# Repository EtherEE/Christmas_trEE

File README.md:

# Christmas tree lamp
> Christmas tree lamp prepared for a child's school Christmas market.

## Table of contents
* [General info](#general-info)
* [Topology](#topology)
* [Technologies](#technologies)
* [PCB](#pcb)
* [Setup](#setup)
* [Main components selection](#main-components-selection)
* [Status](#status)
* [License](#license)

## General info
Luminous Christmas tree-shaped light controlled by touch/proximity. The lamp uses a side-lit fiber optic as the luminous element. The light source is an LED module in white color. LED modules in red, green, blue are also available. Changing the LED module will require setting a different supply voltage on the DC/DC inverter and current verification. The lamp is powered by a battery. The capacity of the battery is sufficient to power the lamp through the night. The battery is charged via a USB type C port. The maximum total current of charging and lighting does not exceed 1 A. When the battery is charging, the D2 LED is lit, which produces a blue glow under the base of the lamp. The skeleton of the lamp and the embedding of the side-lighting fiber on it is a matter of individual taste. This is the most difficult part of the project and its execution directly affects the final result. I built the skeleton from stiff cardboard reinforced with wikol glue and wrapped the skeleton with white yarn. I mounted the LED module on plastic flat bars and glued them with hot glue to the inner parts of the skeleton.
Base width: 14 cm. The height of the lamp is 33 cm. 

## Topology

## Technologies
* Main luminous technology: Mentor M-FIBRE
* KiCAD as an EDA

## PCB

## Setup
Battery charging from USB type C socket with 500mA current set with PROG resistor R2 of 2k.
Sensor touch/proximity sensitivity adjustable with capacitor C7.

## Main components selection
* LED module
  Mentor 1330.0002; White; 1W; 3,3V; 150mA; Imax=300mA;
* Side-lit fiber
  Mentor 1330.1006; 1,5 m; white
* Battery
  Batimex LP505060; Li-Po; 3,7V; 2000mAh. The battery has built in overcharging, overdischarging and over current protection mechnisms.
  Dimensions: length：50mm Max, width： 60,5mm Max, thickness: 5mm Max
* DC/DC converter
  MCP1601-I/MS; Input voltage 2,7-5,5V; Output voltage 0,8-5V. Chip is not needed but good to have as an additional protection for expensive LED module.
  One mode of operation (LDO mode) occurs when the input voltage approaches the output voltage and the BUCK duty cycle approaches 100%. The MCP1601 will enter a low drop out mode and the high-side P-Channel BUCK switch will saturate, providing the output with the maximum voltage possible. 
* LED driver
  MIC4801YM; SO8; 600mA; 0÷5,5V; Ch: 1; 3÷5,5VDC; It features a typical dropout of 50mV at 150mA, LED voltage: 0-Vin
* Touch sensor
  AT42QT1012; One-channel Toggle-mode QTouch® Touch Sensor IC with Power Management Functions
* Battery charger
  MCP73831T-2ACI/OT; Supply voltage: 3,75 - 6V; 4,2V output voltage model; Programmable charge current: 15mA - 500mA;  

## Status
Project is: _finished_.

## License
This project is licensed under the MIT License - see the LICENSE file for details

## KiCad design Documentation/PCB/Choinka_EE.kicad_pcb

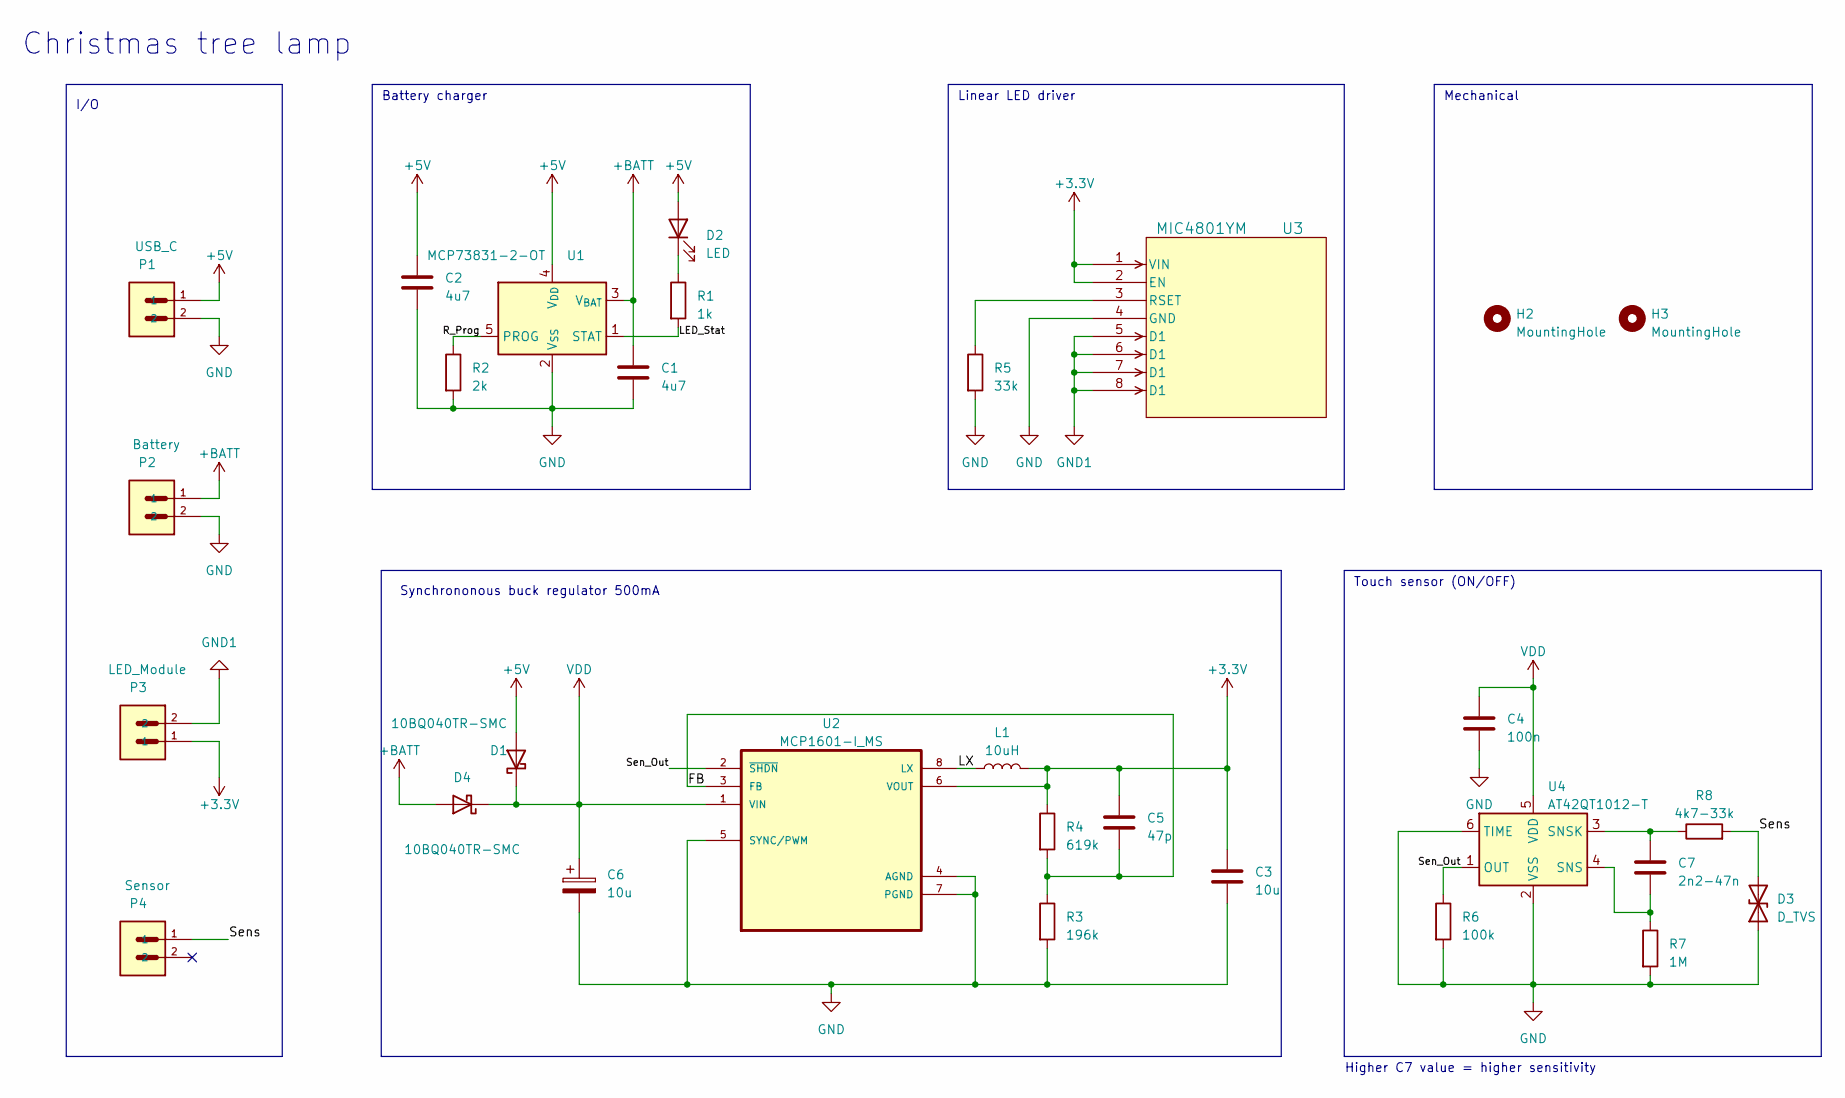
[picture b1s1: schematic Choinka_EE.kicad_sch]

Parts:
C1, C2: 4u7; C_0805_2012Metric_Pad1.18x1.45mm_HandSolder
C3: 10u; C_0805_2012Metric_Pad1.18x1.45mm_HandSolder
C4: 100n; C_0603_1608Metric_Pad1.08x0.95mm_HandSolder
C5: 47p; C_0805_2012Metric_Pad1.18x1.45mm_HandSolder
C6: 10u; CP_EIA-3528-21_Kemet-B_Pad1.50x2.35mm_HandSolder
C7: 2n2-47n; C_0603_1608Metric_Pad1.08x0.95mm_HandSolder
D1, D4: 10BQ040TR-SMC; D_SMB
D2: LED; LED_0603_1608Metric_Pad1.05x0.95mm_HandSolder
D3: D_TVS; C_0603_1608Metric_Pad1.08x0.95mm_HandSolder
H2, H3: MountingHole; MountingHole_3.2mm_M3
L1: 10uH; L_Taiyo-Yuden_MD-4040
P1: USB_C; JST_S2B-PH-SM4-TB
P2: Battery; JST_S2B-PH-SM4-TB
P3: LED_Module; JST_S2B-PH-SM4-TB
P4: Sensor; JST_S2B-PH-SM4-TB
R1: 1k; R_0603_1608Metric_Pad0.98x0.95mm_HandSolder
R2: 2k; R_0603_1608Metric_Pad0.98x0.95mm_HandSolder
R3: 196k; R_0603_1608Metric_Pad0.98x0.95mm_HandSolder
R4: 619k; R_0603_1608Metric_Pad0.98x0.95mm_HandSolder
R5: 33k; R_0805_2012Metric_Pad1.20x1.40mm_HandSolder
R6: 100k; R_0603_1608Metric_Pad0.98x0.95mm_HandSolder
R7: 1M; R_0603_1608Metric_Pad0.98x0.95mm_HandSolder
R8: 4k7-33k; R_0805_2012Metric_Pad1.20x1.40mm_HandSolder
U1: MCP73831-2-OT; SOT-23-5
U2: MCP1601-I_MS; SOP65P490X110-8N
U3: MIC4801YM; SOIC-8_M_MCL-M
U4: AT42QT1012-T; SOT-23-6

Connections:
+3.3V: C3.1, C5.1, L1.2, P3.1, R4.1, U2.6 (VOUT), U3.1 (VIN), U3.2 (EN)
+5V: C2.1, D1.2 (A), D2.2 (A), P1.1, U1.4 (V_{DD})
+BATT: C1.1, D4.2 (A), P2.1, U1.3 (V_{BAT})
/FB: C5.2, R3.1, R4.2, U2.3 (FB)
/LED_Stat: R1.2, U1.1 (STAT)
/LX: L1.1, U2.8 (LX)
/R_Prog: R2.1, U1.5 (PROG)
/Sen_Out: R6.1, U2.2 (~SHDN), U4.1 (OUT)
/Sens: D3.2 (A2), P4.1, R8.2
GND: C1.2, C2.2, C3.2, C4.2, C6.2, D3.1 (A1), P1.2, P2.2, R2.2, R3.2, R5.2, R6.2, R7.2, U1.2 (V_{SS}), U2.4 (AGND), U2.5 (SYNC/PWM), U2.7 (PGND), U3.4 (GND), U4.2 (VSS), U4.6 (TIME)
GND1: P3.2, U3.5 (D1), U3.6 (D1), U3.7 (D1), U3.8 (D1)
unnamed: D2.1 (K), R1.1
unnamed: R5.1, U3.3 (RSET)
unnamed: C7.2, R7.1, U4.4 (SNS)
unnamed: C7.1, R8.1, U4.3 (SNSK)
VDD: C4.1, C6.1, D1.1 (K), D4.1 (K), U2.1 (VIN), U4.5 (VDD)

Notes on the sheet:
Synchrononous buck regulator 500mA
Battery charger
Mechanical
Linear LED driver
Touch sensor (ON/OFF)
I/O
Higher C7 value = higher sensitivity
Christmas tree lamp

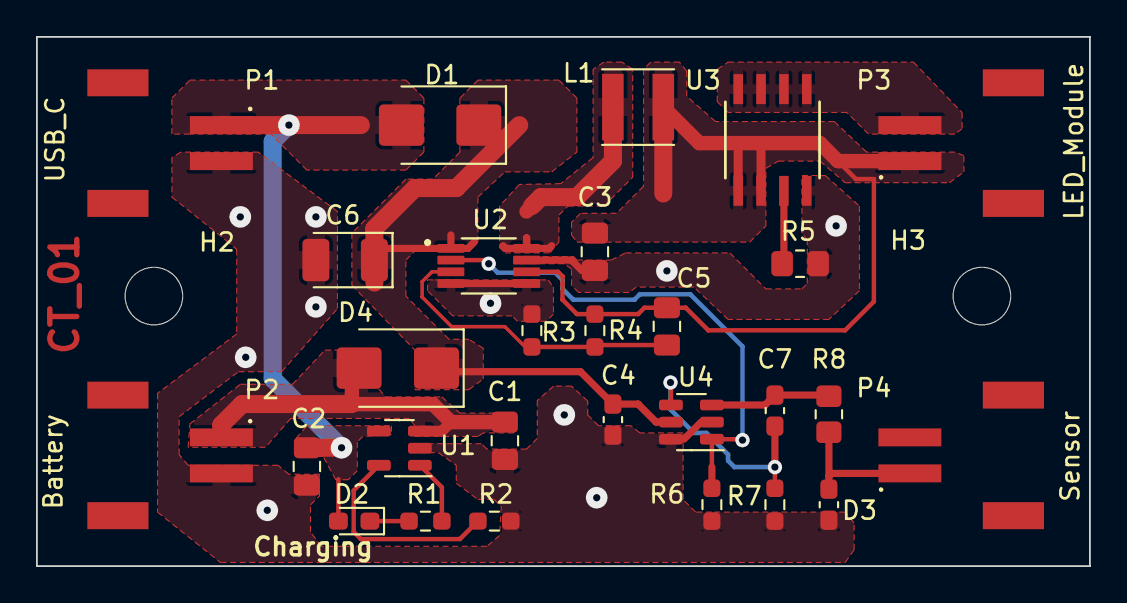
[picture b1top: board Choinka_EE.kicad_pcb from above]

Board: 2 copper layers, 58.5 x 29.4 mm, 30 parts (0 on the bottom side), 16 nets.

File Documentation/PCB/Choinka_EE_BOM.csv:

Id;Oznaczenie;Footprint;Liczba;Oznaczenie;Dostawca i numer artykułu
1;H3,H2;MountingHole_3.2mm_M3;2;MountingHole;
2;D4,D1;D_SMB;2;10BQ040TR-SMC;
3;C2,C1;C_0805_2012Metric_Pad1.18x1.45mm_HandSolder;2;4u7;
4;D3;C_0603_1608Metric_Pad1.08x0.95mm_HandSolder;1;D_TVS;
5;R5;R_0805_2012Metric_Pad1.20x1.40mm_HandSolder;1;33k;
6;P3;JST_S2B-PH-SM4-TB;1;LED_Module;
7;U1;SOT-23-5;1;MCP73831-2-OT;
8;U2;SOP65P490X110-8N;1;MCP1601-I_MS;
9;C4;C_0603_1608Metric_Pad1.08x0.95mm_HandSolder;1;100n;
10;R7;R_0603_1608Metric_Pad0.98x0.95mm_HandSolder;1;1M;
11;R8;R_0805_2012Metric_Pad1.20x1.40mm_HandSolder;1;4k7-33k;
12;U4;SOT-23-6;1;AT42QT1012-T;
13;U3;SOIC-8_M_MCL-M;1;MIC4801YM;
14;C6;CP_EIA-3528-21_Kemet-B_Pad1.50x2.35mm_HandSolder;1;10u;
15;R3;R_0603_1608Metric_Pad0.98x0.95mm_HandSolder;1;196k;
16;L1;L_Taiyo-Yuden_MD-4040;1;10uH;
17;R1;R_0603_1608Metric_Pad0.98x0.95mm_HandSolder;1;1k;
18;P1;JST_S2B-PH-SM4-TB;1;USB_C;
19;C7;C_0603_1608Metric_Pad1.08x0.95mm_HandSolder;1;2n2-47n;
20;D2;LED_0603_1608Metric_Pad1.05x0.95mm_HandSolder;1;LED;
21;C3;C_0805_2012Metric_Pad1.18x1.45mm_HandSolder;1;10u;
22;R6;R_0603_1608Metric_Pad0.98x0.95mm_HandSolder;1;100k;
23;P2;JST_S2B-PH-SM4-TB;1;Battery;
24;R2;R_0603_1608Metric_Pad0.98x0.95mm_HandSolder;1;2k;
25;P4;JST_S2B-PH-SM4-TB;1;Sensor;
26;C5;C_0805_2012Metric_Pad1.18x1.45mm_HandSolder;1;47p;
27;R4;R_0603_1608Metric_Pad0.98x0.95mm_HandSolder;1;619k;

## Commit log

2023-11-19 Rename REDME.md to README.md
2023-11-19 Update README.md
    Add battery
2023-11-19 Update README.md
    LED module
2023-11-19 Dodano Diagram.drawio
2023-11-19 Update README.md
    Diagram
2023-11-19 Dodano Diagram.drawio.svg
2023-11-19 Update README.md
    Topology
2023-12-10 Create empty
2023-12-10 Update LICENSE
